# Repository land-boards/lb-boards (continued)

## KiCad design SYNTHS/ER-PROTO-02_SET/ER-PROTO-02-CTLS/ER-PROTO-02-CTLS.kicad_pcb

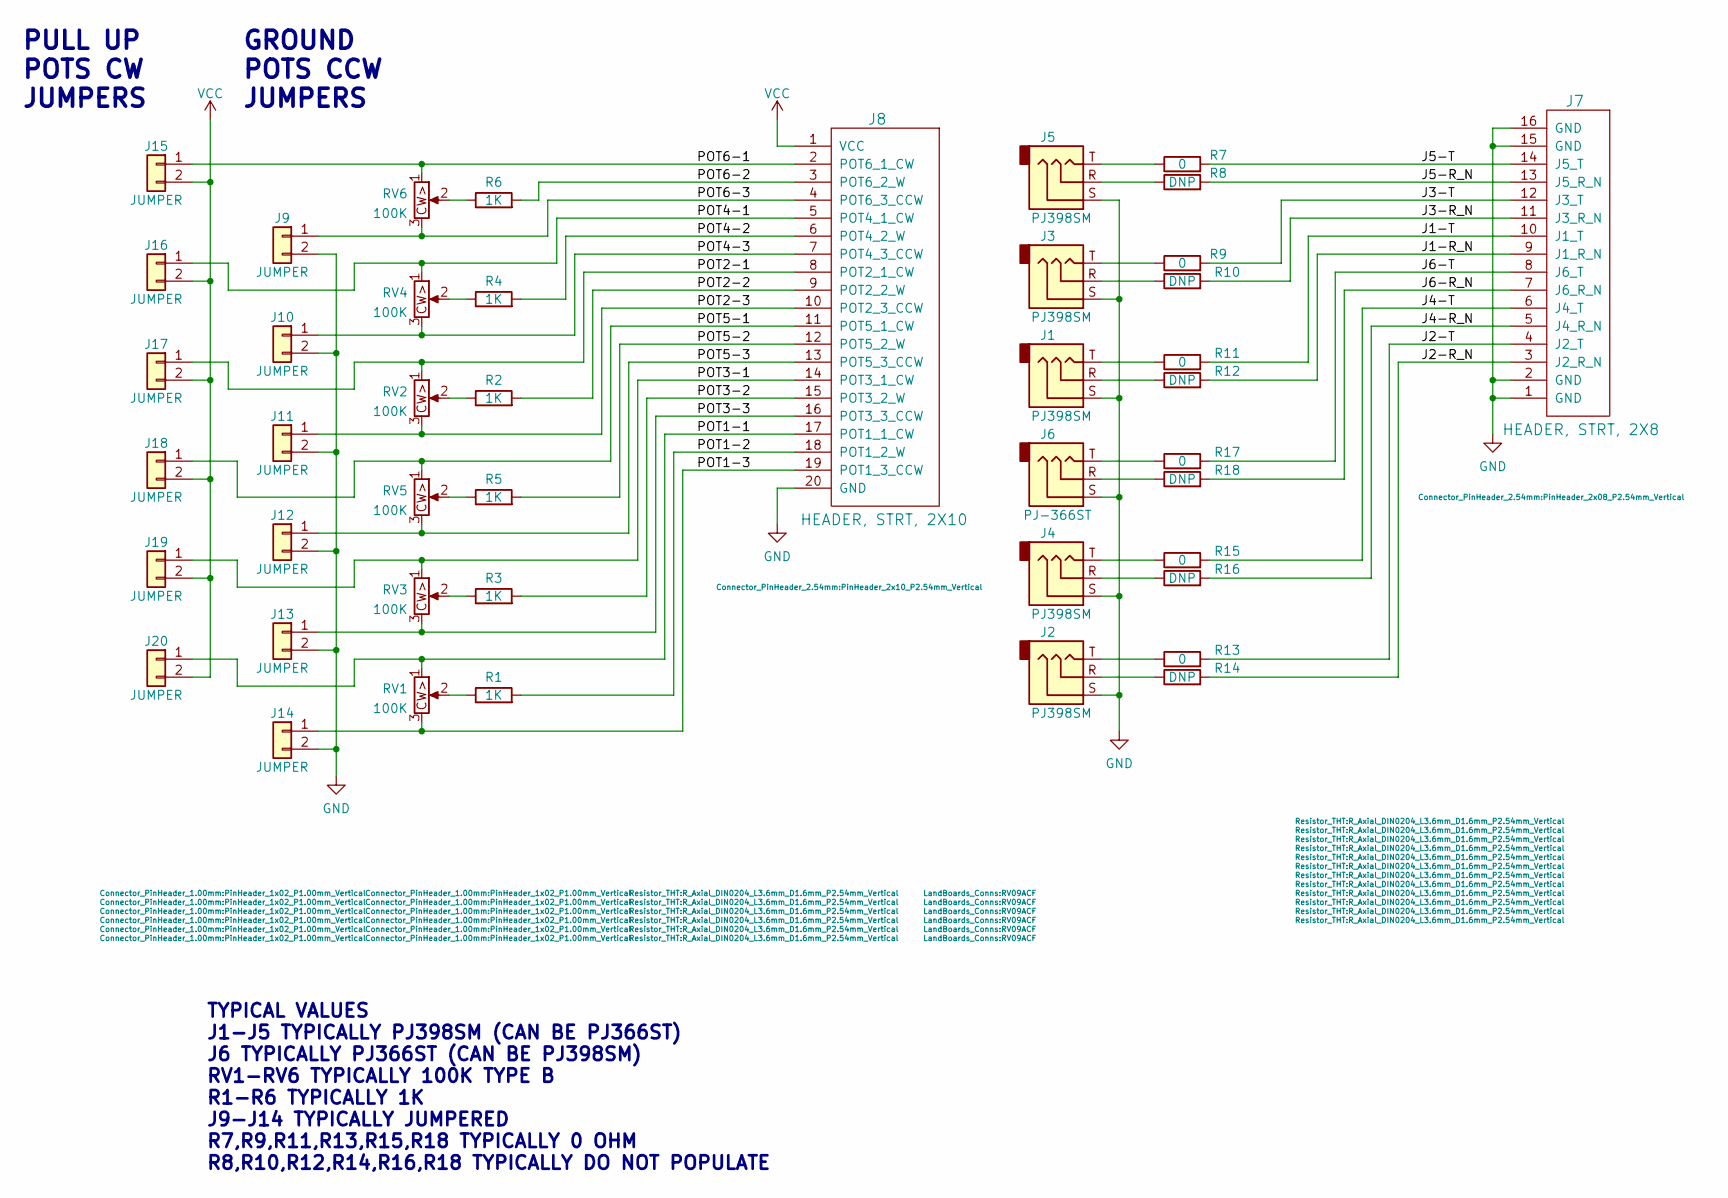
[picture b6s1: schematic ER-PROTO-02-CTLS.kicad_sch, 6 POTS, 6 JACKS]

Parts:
J1, J2, J3, J4, J5: PJ398SM; Jack_3.5mm_QingPu_WQP-PJ366ST_Vertical
J6: PJ-366ST; Jack_3.5mm_QingPu_WQP-PJ366ST_Vertical
J7: HEADER, STRT, 2X8; PinHeader_2x08_P2.54mm_Vertical
J8: HEADER, STRT, 2X10; PinHeader_2x10_P2.54mm_Vertical
J9, J10, J11, J12, J13, J14, J15, J16, J17, J18, J19, J20: JUMPER; PinHeader_1x02_P1.00mm_Vertical
R1, R2, R3, R4, R5, R6: 1K; R_Axial_DIN0204_L3.6mm_D1.6mm_P2.54mm_Vertical
R7, R9, R11, R13, R15, R17: 0; R_Axial_DIN0204_L3.6mm_D1.6mm_P2.54mm_Vertical
R8, R10, R12, R14, R16, R18: DNP; R_Axial_DIN0204_L3.6mm_D1.6mm_P2.54mm_Vertical
RV1, RV2, RV3, RV4, RV5, RV6: 100K; RV09ACF

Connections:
/J1-R_N: J7.9 (J1_R_N), R12.2
/J1-T: J7.10 (J1_T), R11.2
/J2-R_N: J7.3 (J6_R_N), R14.2
/J2-T: J7.4 (J6_T), R13.2
/J3-R_N: J7.11 (J3_R_N), R10.2
/J3-T: J7.12 (J3_T), R9.2
/J4-R_N: J7.5 (J4_R_N), R16.2
/J4-T: J7.6 (J4_T), R15.2
/J5-R_N: J7.13 (J5_R_N), R8.2
/J5-T: J7.14 (J5_T), R7.2
/J6-R_N: J7.7 (J2_R_N), R18.2
/J6-T: J7.8 (J2_T), R17.2
/POT1-1: J8.17 (POT1_1_CW), J20.1, RV1.1
/POT1-2: J8.18 (POT1_2_W), R1.2
/POT1-3: J8.19 (POT1_3_CCW), J14.1, RV1.3
/POT2-1: J8.8 (POT2_1_CW), J17.1, RV2.1
/POT2-2: J8.9 (POT2_2_W), R2.2
/POT2-3: J8.10 (POT2_3_CCW), J11.1, RV2.3
/POT3-1: J8.14 (POT3_1_CW), J19.1, RV3.1
/POT3-2: J8.15 (POT3_2_W), R3.2
/POT3-3: J8.16 (POT3_3_CCW), J13.1, RV3.3
/POT4-1: J8.5 (POT4_1_CW), J16.1, RV4.1
/POT4-2: J8.6 (POT4_2_W), R4.2
/POT4-3: J8.7 (POT4_3_CCW), J10.1, RV4.3
/POT5-1: J8.11 (POT5_1_CW), J18.1, RV5.1
/POT5-2: J8.12 (POT5_2_W), R5.2
/POT5-3: J8.13 (POT5_3_CCW), J12.1, RV5.3
/POT6-1: J8.2 (POT6_1_CW), J15.1, RV6.1
/POT6-2: J8.3 (POT6_2_W), R6.2
/POT6-3: J8.4 (POT6_3_CCW), J9.1, RV6.3
GND: J1.S, J2.S, J3.S, J4.S, J5.S, J6.S, J7.1 (GND), J7.2 (GND), J7.15 (GND), J7.16 (GND), J8.20 (GND), J9.2, J10.2, J11.2, J12.2, J13.2, J14.2
unnamed: J1.R, R12.1
unnamed: J1.T, R11.1
unnamed: J2.R, R14.1
unnamed: J2.T, R13.1
unnamed: J3.R, R10.1
unnamed: J3.T, R9.1
unnamed: J4.R, R16.1
unnamed: J4.T, R15.1
unnamed: J5.R, R8.1
unnamed: J5.T, R7.1
unnamed: J6.R, R18.1
unnamed: J6.T, R17.1
unnamed: R1.1, RV1.2
unnamed: R2.1, RV2.2
unnamed: R3.1, RV3.2
unnamed: R4.1, RV4.2
unnamed: R5.1, RV5.2
unnamed: R6.1, RV6.2
VCC: J8.1 (VCC), J15.2, J16.2, J17.2, J18.2, J19.2, J20.2

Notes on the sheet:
TYPICAL VALUES J1-J5 TYPICALLY PJ398SM (CAN BE PJ366ST) J6 TYPICALLY PJ366ST (CAN BE PJ398SM) RV1-RV6 TYPICALLY 100K TYPE B R1-R6 TYPICALLY 1K J9-J14 TYPICALLY JUMPERED R7,R9,R11,R13,R15,R18 TYPICALLY 0 OHM R8,R10,R12,R14,R16,R18 TYPICALLY DO NOT POPULATE
GROUND POTS CCW JUMPERS
PULL UP POTS CW JUMPERS

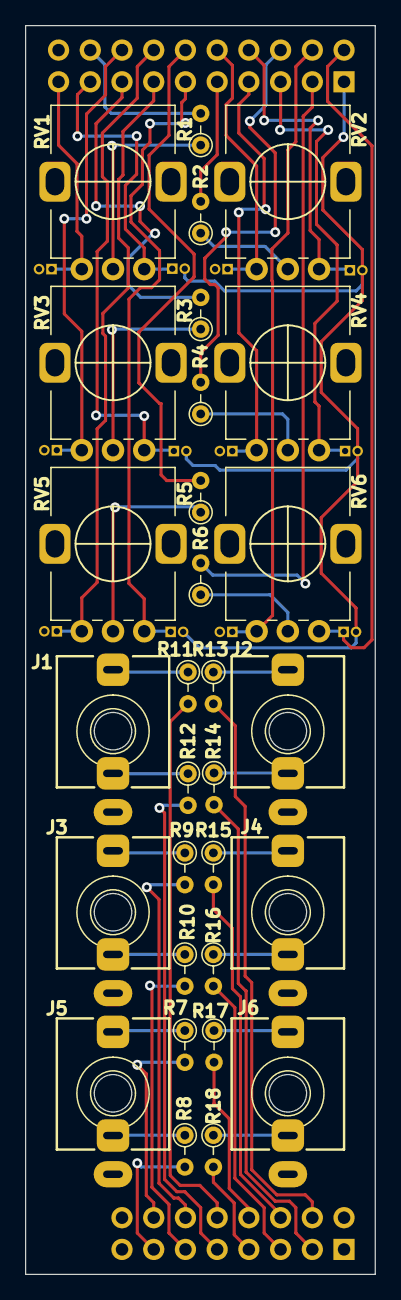
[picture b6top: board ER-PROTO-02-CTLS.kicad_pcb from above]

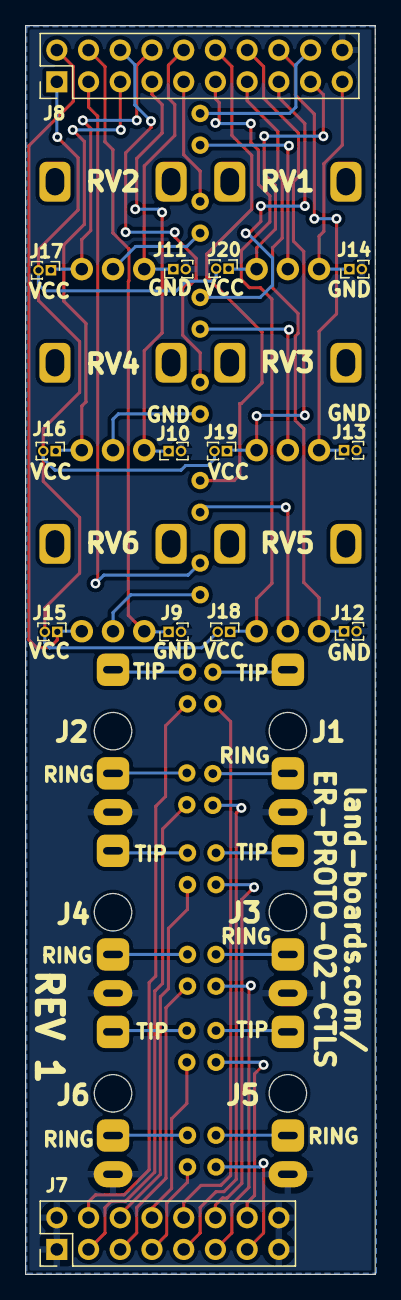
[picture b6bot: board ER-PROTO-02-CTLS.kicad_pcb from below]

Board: 2 copper layers, 28.0 x 100.0 mm, 44 parts (14 on the bottom side), 50 nets.

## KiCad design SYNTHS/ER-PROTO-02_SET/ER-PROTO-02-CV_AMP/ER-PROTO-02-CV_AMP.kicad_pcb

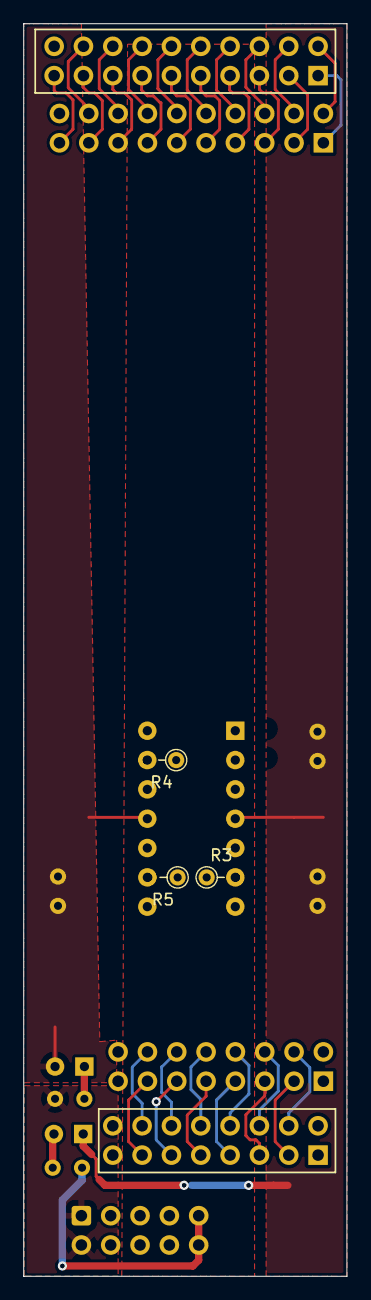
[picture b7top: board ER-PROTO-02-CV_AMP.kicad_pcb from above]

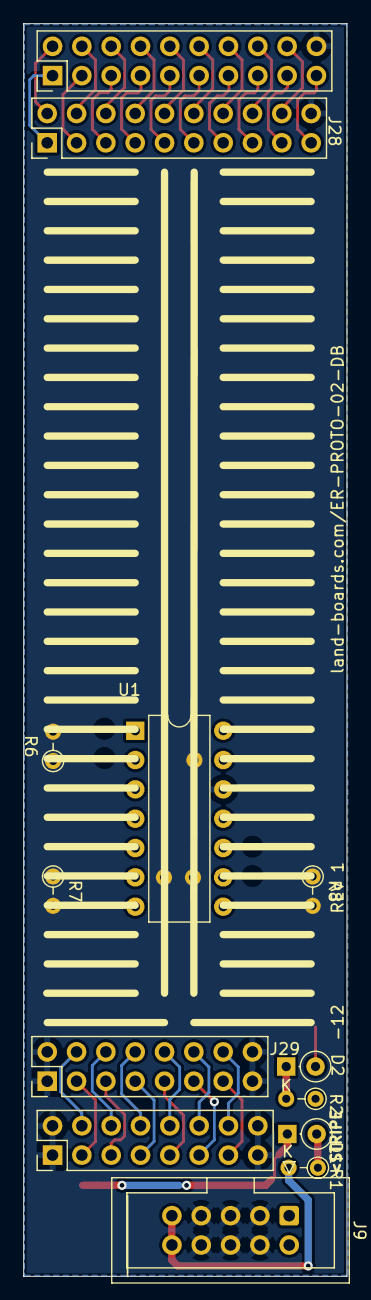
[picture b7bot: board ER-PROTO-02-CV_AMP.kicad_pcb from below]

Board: 2 copper layers, 28.0 x 108.5 mm, 16 parts (13 on the bottom side), 42 nets.

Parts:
D1, D2: BAT41; D_DO-35_SOD27_P2.54mm_Vertical_KathodeUp
J7, J29: PROTO02_JACKS; PinHeader_2x08_P2.54mm_Vertical
J8, J28: PROTO02_POTS; PinHeader_2x10_P2.54mm_Vertical
J9: ER-PWR-2X5; IDC-Header_2x05_P2.54mm_Vertical
R1, R2: 10; R_Axial_DIN0204_L3.6mm_D1.6mm_P2.54mm_Vertical
R3, R4, R5, R6, R7, R8: 10K; R_Axial_DIN0204_L3.6mm_D1.6mm_P2.54mm_Vertical
U1: TL074; DIP-14_W7.62mm

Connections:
+5V: J8.1 (VCC), J28.1 (VCC)
+12V: D1.1 (K), U1.4 (V+)
+12VA: J9.9 (+12V), J9.10 (+12V), R1.2
-12V: D2.2 (A), U1.11 (V-)
-12VA: J9.1 (-12V), J9.2 (-12V), R2.1
/J1-R_N: J7.9 (J1_R_N), J29.9 (J1_R_N)
/J1-T: J7.10 (J1_T), J29.10 (J1_T), U1.3 (+)
/J2-R_N: J7.7 (J2_R_N), J29.7 (J2_R_N)
/J2-T: J7.8 (J2_T), J29.8 (J2_T), R6.2, U1.1
/J3-R_N: J7.11 (J3_R_N), J29.11 (J3_R_N)
/J3-T: J7.12 (J3_T), J29.12 (J3_T), U1.5 (+)
/J4-R_N: J7.5 (J4_R_N), J29.5 (J4_R_N)
/J4-T: J7.6 (J4_T), J29.6 (J4_T), R7.2, U1.7
/J5-R_N: J7.13 (J5_R_N), J29.13 (J5_R_N)
/J5-T: J7.14 (J5_T), J29.14 (J5_T), U1.10 (+)
/J6-R_N: J7.3 (J6_R_N), J29.3 (J6_R_N)
/J6-T: J7.4 (J6_T), J29.4 (J6_T), R8.2, U1.8
/POT1-1: J8.17 (POT1_1_CW), J28.17 (POT1_1_CW)
/POT1-2: J8.18 (POT1_2_W), J28.18 (POT1_2_W)
/POT1-3: J8.19 (POT1_3_CCW), J28.19 (POT1_3_CCW)
/POT2-1: J8.8 (POT2_1_CW), J28.8 (POT2_1_CW)
/POT2-2: J8.9 (POT2_2_W), J28.9 (POT2_2_W)
/POT2-3: J8.10 (POT2_3_CCW), J28.10 (POT2_3_CCW)
/POT3-1: J8.14 (POT3_1_CW), J28.14 (POT3_1_CW)
/POT3-2: J8.15 (POT3_2_W), J28.15 (POT3_2_W)
/POT3-3: J8.16 (POT3_3_CCW), J28.16 (POT3_3_CCW)
/POT4-1: J8.5 (POT4_1_CW), J28.5 (POT4_1_CW)
/POT4-2: J8.6 (POT4_2_W), J28.6 (POT4_2_W)
/POT4-3: J8.7 (POT4_3_CCW), J28.7 (POT4_3_CCW)
/POT5-1: J8.11 (POT5_1_CW), J28.11 (POT5_1_CW)
/POT5-2: J8.12 (POT5_2_W), J28.12 (POT5_2_W)
/POT5-3: J8.13 (POT5_3_CCW), J28.13 (POT5_3_CCW)
/POT6-1: J8.2 (POT6_1_CW), J28.2 (POT6_1_CW)
/POT6-2: J8.3 (POT6_2_W), J28.3 (POT6_2_W)
/POT6-3: J8.4 (POT6_3_CCW), J28.4 (POT6_3_CCW)
GND: J7.1 (GND), J7.2 (GND), J7.15 (GND), J7.16 (GND), J8.20 (GND), J9.3 (GND), J9.4 (GND), J9.5 (GND), J9.6 (GND), J9.7 (GND), J9.8 (GND), J28.20 (GND), J29.1 (GND), J29.2 (GND), J29.15 (GND), J29.16 (GND), R3.1, R4.1, R5.1, U1.12 (+)
unnamed: D1.2 (A), R1.1
unnamed: D2.1 (K), R2.2
unnamed: R5.2, R7.1, U1.6 (-)
unnamed: R4.2, R6.1, U1.2 (-)
unnamed: R3.2, R8.1, U1.9 (-)
unnamed: U1.13 (-), U1.14

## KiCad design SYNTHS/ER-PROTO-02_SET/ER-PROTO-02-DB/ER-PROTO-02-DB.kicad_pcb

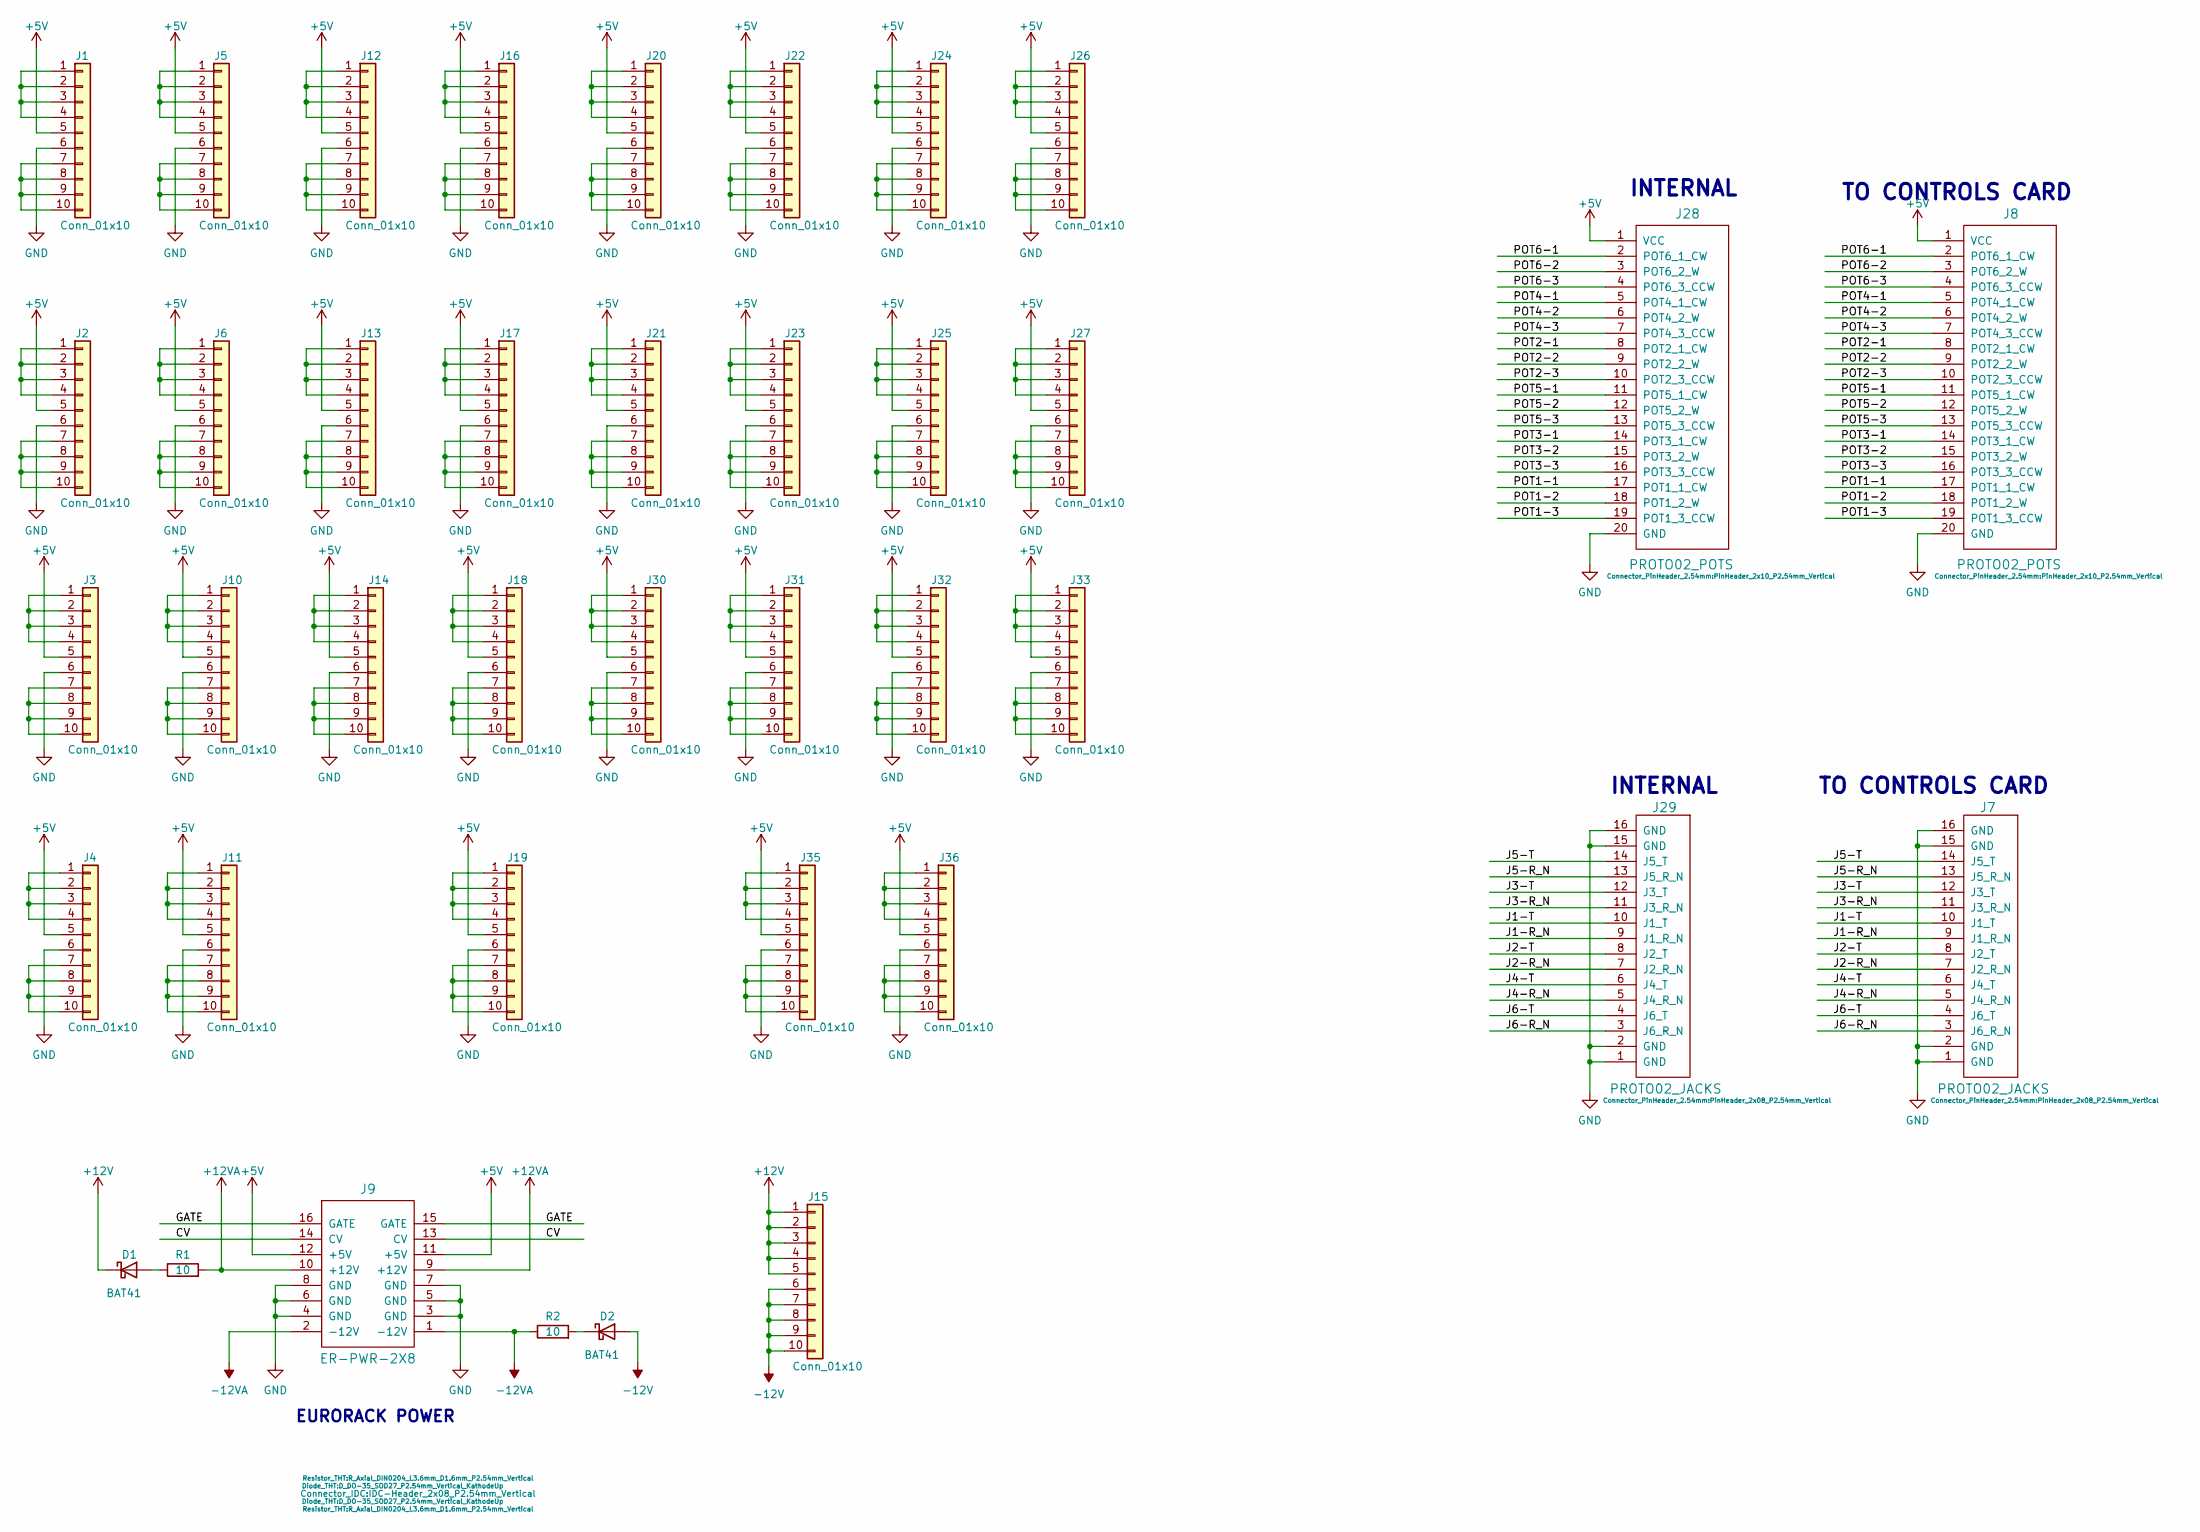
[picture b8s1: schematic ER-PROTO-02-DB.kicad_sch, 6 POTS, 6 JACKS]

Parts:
D1, D2: BAT41; D_DO-35_SOD27_P2.54mm_Vertical_KathodeUp
J1, J2, J3, J4, J5, J6, J10, J11, J12, J13, J14, J15, J16, J17, J18, J19, J20, J21, J22, J23, J24, J25, J26, J27, J30, J31, J32, J33, J35, J36: Conn_01x10; PinHeader_1x10_P2.54mm_Vertical
J7, J29: PROTO02_JACKS; PinHeader_2x08_P2.54mm_Vertical
J8, J28: PROTO02_POTS; PinHeader_2x10_P2.54mm_Vertical
J9: ER-PWR-2X8; IDC-Header_2x08_P2.54mm_Vertical
R1, R2: 10; R_Axial_DIN0204_L3.6mm_D1.6mm_P2.54mm_Vertical

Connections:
+5V: J1.5, J2.5, J3.5, J4.5, J5.5, J6.5, J8.1 (VCC), J9.11 (+5V), J9.12 (+5V), J10.5, J11.5, J12.5, J13.5, J14.5, J16.5, J17.5, J18.5, J19.5, J20.5, J21.5, J22.5, J23.5, J24.5, J25.5, J26.5, J27.5, J28.1 (VCC), J30.5, J31.5, J32.5, J33.5, J35.5, J36.5
+12V: D1.1 (K), J15.1, J15.2, J15.3, J15.4, J15.5
+12VA: J9.9 (+12V), J9.10 (+12V), R1.2
-12V: D2.2 (A), J15.6, J15.7, J15.8, J15.9, J15.10
-12VA: J9.1 (-12V), J9.2 (-12V), R2.1
/CV: J9.13 (CV), J9.14 (CV)
/GATE: J9.15 (GATE), J9.16 (GATE)
/J1-R_N: J7.9 (J1_R_N), J29.9 (J1_R_N)
/J1-T: J7.10 (J1_T), J29.10 (J1_T)
/J2-R_N: J7.7 (J2_R_N), J29.7 (J2_R_N)
/J2-T: J7.8 (J2_T), J29.8 (J2_T)
/J3-R_N: J7.11 (J3_R_N), J29.11 (J3_R_N)
/J3-T: J7.12 (J3_T), J29.12 (J3_T)
/J4-R_N: J7.5 (J4_R_N), J29.5 (J4_R_N)
/J4-T: J7.6 (J4_T), J29.6 (J4_T)
/J5-R_N: J7.13 (J5_R_N), J29.13 (J5_R_N)
/J5-T: J7.14 (J5_T), J29.14 (J5_T)
/J6-R_N: J7.3 (J6_R_N), J29.3 (J6_R_N)
/J6-T: J7.4 (J6_T), J29.4 (J6_T)
/POT1-1: J8.17 (POT1_1_CW), J28.17 (POT1_1_CW)
/POT1-2: J8.18 (POT1_2_W), J28.18 (POT1_2_W)
/POT1-3: J8.19 (POT1_3_CCW), J28.19 (POT1_3_CCW)
/POT2-1: J8.8 (POT2_1_CW), J28.8 (POT2_1_CW)
/POT2-2: J8.9 (POT2_2_W), J28.9 (POT2_2_W)
/POT2-3: J8.10 (POT2_3_CCW), J28.10 (POT2_3_CCW)
/POT3-1: J8.14 (POT3_1_CW), J28.14 (POT3_1_CW)
/POT3-2: J8.15 (POT3_2_W), J28.15 (POT3_2_W)
/POT3-3: J8.16 (POT3_3_CCW), J28.16 (POT3_3_CCW)
/POT4-1: J8.5 (POT4_1_CW), J28.5 (POT4_1_CW)
/POT4-2: J8.6 (POT4_2_W), J28.6 (POT4_2_W)
/POT4-3: J8.7 (POT4_3_CCW), J28.7 (POT4_3_CCW)
/POT5-1: J8.11 (POT5_1_CW), J28.11 (POT5_1_CW)
/POT5-2: J8.12 (POT5_2_W), J28.12 (POT5_2_W)
/POT5-3: J8.13 (POT5_3_CCW), J28.13 (POT5_3_CCW)
/POT6-1: J8.2 (POT6_1_CW), J28.2 (POT6_1_CW)
/POT6-2: J8.3 (POT6_2_W), J28.3 (POT6_2_W)
/POT6-3: J8.4 (POT6_3_CCW), J28.4 (POT6_3_CCW)
GND: J1.6, J2.6, J3.6, J4.6, J5.6, J6.6, J7.1 (GND), J7.2 (GND), J7.15 (GND), J7.16 (GND), J8.20 (GND), J9.3 (GND), J9.4 (GND), J9.5 (GND), J9.6 (GND), J9.7 (GND), J9.8 (GND), J10.6, J11.6, J12.6, J13.6, J14.6, J16.6, J17.6, J18.6, J19.6, J20.6, J21.6, J22.6, J23.6, J24.6, J25.6, J26.6, J27.6, J28.20 (GND), J29.1 (GND), J29.2 (GND), J29.15 (GND), J29.16 (GND), J30.6, J31.6, J32.6, J33.6, J35.6, J36.6
unnamed: D1.2 (A), R1.1
unnamed: D2.1 (K), R2.2
unnamed: J1.1, J1.2, J1.3, J1.4
unnamed: J1.7, J1.8, J1.9, J1.10
unnamed: J2.1, J2.2, J2.3, J2.4
unnamed: J2.7, J2.8, J2.9, J2.10
unnamed: J3.1, J3.2, J3.3, J3.4
unnamed: J3.7, J3.8, J3.9, J3.10
unnamed: J4.1, J4.2, J4.3, J4.4
unnamed: J4.7, J4.8, J4.9, J4.10
unnamed: J5.1, J5.2, J5.3, J5.4
unnamed: J5.7, J5.8, J5.9, J5.10
unnamed: J6.1, J6.2, J6.3, J6.4
unnamed: J6.7, J6.8, J6.9, J6.10
unnamed: J10.1, J10.2, J10.3, J10.4
unnamed: J10.7, J10.8, J10.9, J10.10
unnamed: J11.1, J11.2, J11.3, J11.4
unnamed: J11.7, J11.8, J11.9, J11.10
unnamed: J12.1, J12.2, J12.3, J12.4
unnamed: J12.7, J12.8, J12.9, J12.10
unnamed: J13.1, J13.2, J13.3, J13.4
unnamed: J13.7, J13.8, J13.9, J13.10
unnamed: J14.1, J14.2, J14.3, J14.4
unnamed: J14.7, J14.8, J14.9, J14.10
unnamed: J16.1, J16.2, J16.3, J16.4
unnamed: J16.7, J16.8, J16.9, J16.10
unnamed: J17.1, J17.2, J17.3, J17.4
unnamed: J17.7, J17.8, J17.9, J17.10
unnamed: J18.1, J18.2, J18.3, J18.4
unnamed: J18.7, J18.8, J18.9, J18.10
unnamed: J19.1, J19.2, J19.3, J19.4
unnamed: J19.7, J19.8, J19.9, J19.10
unnamed: J20.1, J20.2, J20.3, J20.4
unnamed: J20.7, J20.8, J20.9, J20.10
unnamed: J21.1, J21.2, J21.3, J21.4
unnamed: J21.7, J21.8, J21.9, J21.10
unnamed: J22.1, J22.2, J22.3, J22.4
unnamed: J22.7, J22.8, J22.9, J22.10
unnamed: J23.1, J23.2, J23.3, J23.4
unnamed: J23.7, J23.8, J23.9, J23.10
unnamed: J24.1, J24.2, J24.3, J24.4
unnamed: J24.7, J24.8, J24.9, J24.10
unnamed: J25.1, J25.2, J25.3, J25.4
unnamed: J25.7, J25.8, J25.9, J25.10
unnamed: J26.1, J26.2, J26.3, J26.4
unnamed: J26.7, J26.8, J26.9, J26.10
unnamed: J27.1, J27.2, J27.3, J27.4
unnamed: J27.7, J27.8, J27.9, J27.10
unnamed: J30.1, J30.2, J30.3, J30.4
unnamed: J30.7, J30.8, J30.9, J30.10
unnamed: J31.1, J31.2, J31.3, J31.4
unnamed: J31.7, J31.8, J31.9, J31.10
unnamed: J32.1, J32.2, J32.3, J32.4
unnamed: J32.7, J32.8, J32.9, J32.10
unnamed: J33.1, J33.2, J33.3, J33.4
unnamed: J33.7, J33.8, J33.9, J33.10
unnamed: J35.1, J35.2, J35.3, J35.4
unnamed: J35.7, J35.8, J35.9, J35.10
unnamed: J36.1, J36.2, J36.3, J36.4
unnamed: J36.7, J36.8, J36.9, J36.10

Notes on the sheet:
EURORACK POWER
TO CONTROLS CARD
INTERNAL

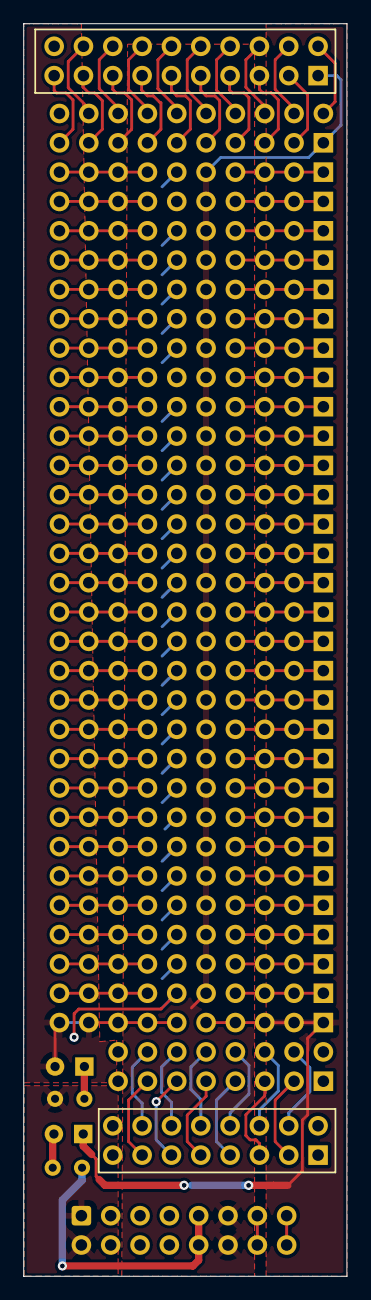
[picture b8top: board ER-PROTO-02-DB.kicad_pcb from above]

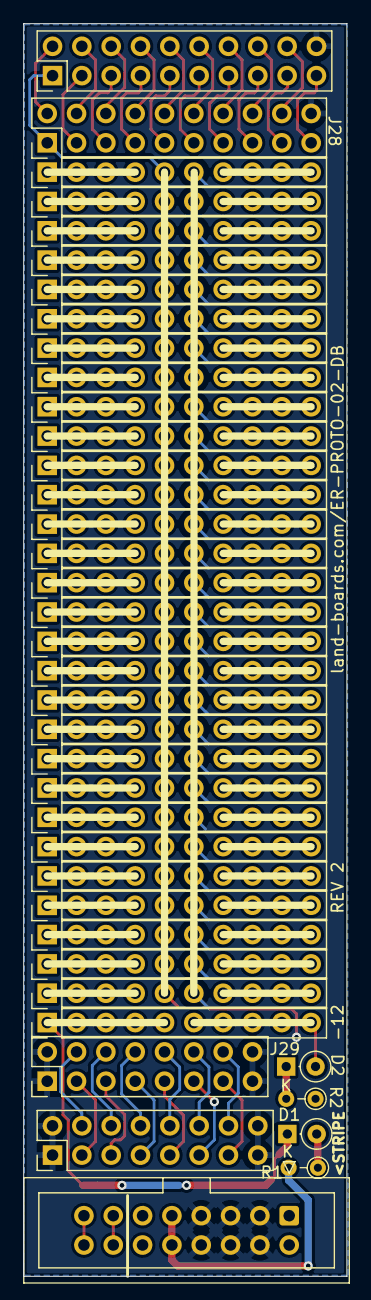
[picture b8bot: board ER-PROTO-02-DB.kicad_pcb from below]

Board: 2 copper layers, 28.0 x 108.5 mm, 39 parts (39 on the bottom side), 98 nets.
